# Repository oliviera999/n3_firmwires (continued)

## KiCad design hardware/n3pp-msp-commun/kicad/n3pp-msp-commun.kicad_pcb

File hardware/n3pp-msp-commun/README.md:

# Carte commune n3pp + msp (KiCad)

**Un seul PCB pour deux stations** : la serre/élevage (**n3pp**) et la station météo
(**msp**) partagent cette carte porteuse pour **ESP32 DevKit V1 30 broches**. Les deux
brochages firmware forment une **union disjointe vérifiée** (aucun GPIO utilisé pour deux
usages différents) : les firmwares actuels tournent **sans aucune modification**, c'est le
**profil d'assemblage** (quels composants on soude) qui spécialise la carte.

```
pinmap.json                  Source de vérité (union n3pp_config.h + msp_config.h, profils par broche)
kicad/n3pp-msp-commun.*      Projet KiCad 8 (schéma, PCB ROUTÉ) — ouvrable KiCad 8/9/10
BOM.csv                      Nomenclature (séparateur ;) avec colonne Profil
ACHATS.md                    Liste d'achat complète par profil (BOM + périphériques + boîtier + outillage)
ASSEMBLAGE-N3PP.md           Feuille d'assemblage générée : quoi souder pour une station n3pp
ASSEMBLAGE-MSP.md            Feuille d'assemblage générée : quoi souder pour une station msp
exports/gerbers-*.zip        Fabrication (Gerbers + perçages) — 210 x 105 mm, 2 couches, rev 0.2
exports/schema.pdf, pcb-*.svg   Rendus pour revue sans KiCad
fritzing/*.fzz               Vue breadboard du câblage (Fritzing >= 1.0)
generator/generate.py        Régénère schéma + PCB (non routé) + BOM + feuilles d'assemblage
generator/route_lv.py        Pipeline de routage (freerouting + couture GND + reliefs)
generator/tidy_silkscreen.py  Range la sérigraphie (repères vs étiquettes)
generator/export_fab.py      Export Gerbers/perçages prêts fabricant + rendus
generator/generate_fritzing.py  Régénère le .fzz de câblage
tools/check_pinmap_vs_firmware.py   Garde anti-dérive DOUBLE : n3pp_config.h ET msp_config.h ↔ plan
```

## Le principe : une base, deux profils

| Profil | Composants à souder | Le firmware tourne tel quel ? |
|---|---|---|
| **commun** | DevKit + alim + **interrupteur d'alim capteurs (GPIO13)** + 5 entrées ADC + pont batterie commuté + I2C/OLED + breakout + distribution | — (socle des deux profils) |
| **n3pp** | + REL2 (pompe GPIO12) + DHT GPIO18 | ✅ `pio run -e esp32dev` (n3pp) |
| **msp** | + servos tracker + 2 DHT + DS18B20 + pluie + 10k LDR | ✅ `pio run -e esp32dev` (msp) |
| **extension** | REL3..REL6 (GPIO 16/17/19/23), à activer côté firmware plus tard | provision matérielle |

Aucun strap, aucun interrupteur : les GPIO des deux firmwares ne se marchent jamais
dessus (voir la table ci-dessous), on peuple ou pas. Les feuilles
[`ASSEMBLAGE-N3PP.md`](ASSEMBLAGE-N3PP.md) / [`ASSEMBLAGE-MSP.md`](ASSEMBLAGE-MSP.md)
sont **générées depuis le même code que le PCB** : elles ne peuvent pas dériver du plan.

## Table des broches (union disjointe)

| GPIO | Bloc carte | n3pp (`n3pp_config.h`) | msp (`msp_config.h`) |
|---|---|---|---|
| 13 | **Interrupteur d'alim capteurs** (Q1+Q7 P-MOSFET → rail `+3V3_SW`) | `RELAIS` | `RELAIS` |
| 12 | **REL2** (strapping MTDI → pull-down base 10k) | `POMPE` | — |
| 16/17/19/23 | **REL3..REL6** extensions AUX | — | — |
| 18 | DHT n3pp (JST, pull-up 10k) | `DHTPIN` | — |
| 26 / 15 | DHT INT / EXT (JST, pull-ups 10k) | — | `DHTPININT` / `DHTPINEXT` |
| 2 | 1-Wire DS18B20 (bornier, pull-up 4,7k) ⚠️ strapping | — | `oneWireBus` |
| 27 | Pluie — **sortie DO numérique** (ADC2 ≠ WiFi) | — | `PLUIE` |
| 33/32/35/34/39 | **ADC A..E** (borniers 3V3/AIN/GND) | `humidite1..4`, `LUMINOSITE` | `LUMINOSITEa..d`, `HumiditeSol` |
| 36 (VP) | Pont batterie 2,2k/2,2k (bornier VBAT/GND) | `pontdiv` | `pontdiv` |
| 25 / 14 | Servos tracker (headers, série 220R) | — | `SERVOGD` / `SERVOHB` |
| 21 / 22 | I2C : OLED 0x3C + **3 ports libres** (pull-ups 4,7k) | ✅ | ✅ |
| 4, 5, EN, RX0, TX0 | **Breakout J18** (tous les GPIO restants) | libres | libres |

## Les demandes spécifiques de cette carte

- **Rail capteurs commuté (rev 0.2)** : les deux firmwares utilisent GPIO13 comme
  *power-gate* (mis à 1 au réveil, relâché en deep sleep — vérifié dans les sources).
  La carte le câble sur un **interrupteur haut P-MOSFET** (Q1 BC337 + Q7 NDP6020P) qui
  coupe `+3V3_SW` — capteurs, OLED, ports I2C **et leurs pull-ups** — pendant la veille.
  Le **pont diviseur batterie est commuté lui aussi** (Q8 BS250 côté haut + Q9), donc
  ~0 µA de fuite en veille, et jamais plus de 3,3 V sur GPIO36 pont coupé.
- **5 canaux relais** embarqués (BC337 + 1N4007 + LED témoin + bornier NO/COM/NC) :
  REL2 piloté par n3pp (pompe), REL3..REL6 en réserve sur des GPIO **non-strapping** —
  à activer côté firmware comme AUX1/AUX2 de ffp5cs, sans retoucher la carte.
- **Connexions I2C supplémentaires** : OLED + 3 ports libres (J15/J16/J17, brochage
  GND/VCC/SCL/SDA), 3-4 modules simultanés avec les pull-ups 4,7 k.
- **Toutes les broches restantes utilisables** : breakout J18 (`3V3 GND EN IO4 IO5 RX0
  TX0` — RX0/TX0 à laisser libres pendant un flash USB), rail d'alim Dupont J19
  (2×5V 2×GND 2×3V3), borniers de distribution 5 V (J28) et 3V3 (J29).
- **Zéro soudure à l'usage** : DevKit socketé, charges sur borniers à vis, capteurs sur
  JST-XH/borniers, servos/OLED/GPIO en headers.

## Pièges connus (hérités des firmwares, choix assumés)

- **GPIO2 (1-Wire msp)** est une broche de strapping : le pull-up 4,7 k peut gêner le
  passage en mode flash. Si le flash USB échoue, débrancher la sonde DS18B20 le temps du
  flash. (Conservé pour rester compatible avec le firmware msp actuel.)
- **GPIO27 (pluie msp)** est sur ADC2, inutilisable en analogique quand le WiFi est actif :
  brancher la sortie **DO** (numérique) du module pluie, pas AO — lue en `digitalRead`
  par le firmware msp ≥ 2.72 (projection 4095 sec / 100 mouillé, contrat serveur inchangé).
- **GPIO12 (pompe n3pp)** est strapping MTDI : le pull-down de base du canal REL2 garantit
  l'état sûr au boot.
- **JP1 (cavalier 3V3)** : en alimentation batterie/LDO par J29, RETIRER le cavalier
  avant de brancher l'USB du DevKit (sinon deux régulateurs se disputent le rail).
- Profils **sur batterie (18650 + TP4056 solaire)** : ne pas peupler les LED témoin,
  et **ne jamais brancher la batterie brute sur J1/jack** (brownouts + relais 5 V) —
  boost 5 V → J1 si relais/servos, ou LDO 3,3 V → J29 sinon ; mesure VBAT → J27.
  Câblages, achats et autonomies chiffrées : [`ACHATS.md` §5 bis](ACHATS.md).

## Régénérer / rerouter / vérifier

```bash
cd hardware/n3pp-msp-commun
python3 generator/generate.py          # schéma + PCB placé (NON routé) + BOM + feuilles
python3 generator/route_lv.py          # autoroute, coud les masses, corrige les reliefs
python3 generator/tidy_silkscreen.py   # écarte les repères qui masquent une étiquette
python3 generator/export_fab.py        # zip Gerbers prêt JLCPCB + rendus de revue
python3 tools/check_pinmap_vs_firmware.py   # garde anti-dérive (les DEUX firmwares)
kicad-cli pcb drc --severity-error kicad/n3pp-msp-commun.kicad_pcb -o /tmp/drc.rpt
```

⚠️ `generate.py` écrase le PCB routé — enchaîner systématiquement avec `route_lv.py`.
Le routage livré dans `kicad/` est déjà fait et validé (DRC 0 violation).

Empreintes : bibliothèque officielle KiCad 8.0.9 (CC-BY-SA 4.0 + exception d'usage),
vendorées dans `generator/footprints/`.

Commander les cartes : voir **[../COMMANDE_JLCPCB.md](../COMMANDE_JLCPCB.md)**
(réglages du formulaire, options utiles, pourquoi 1 oz ici et 2 oz sur la 230 V).

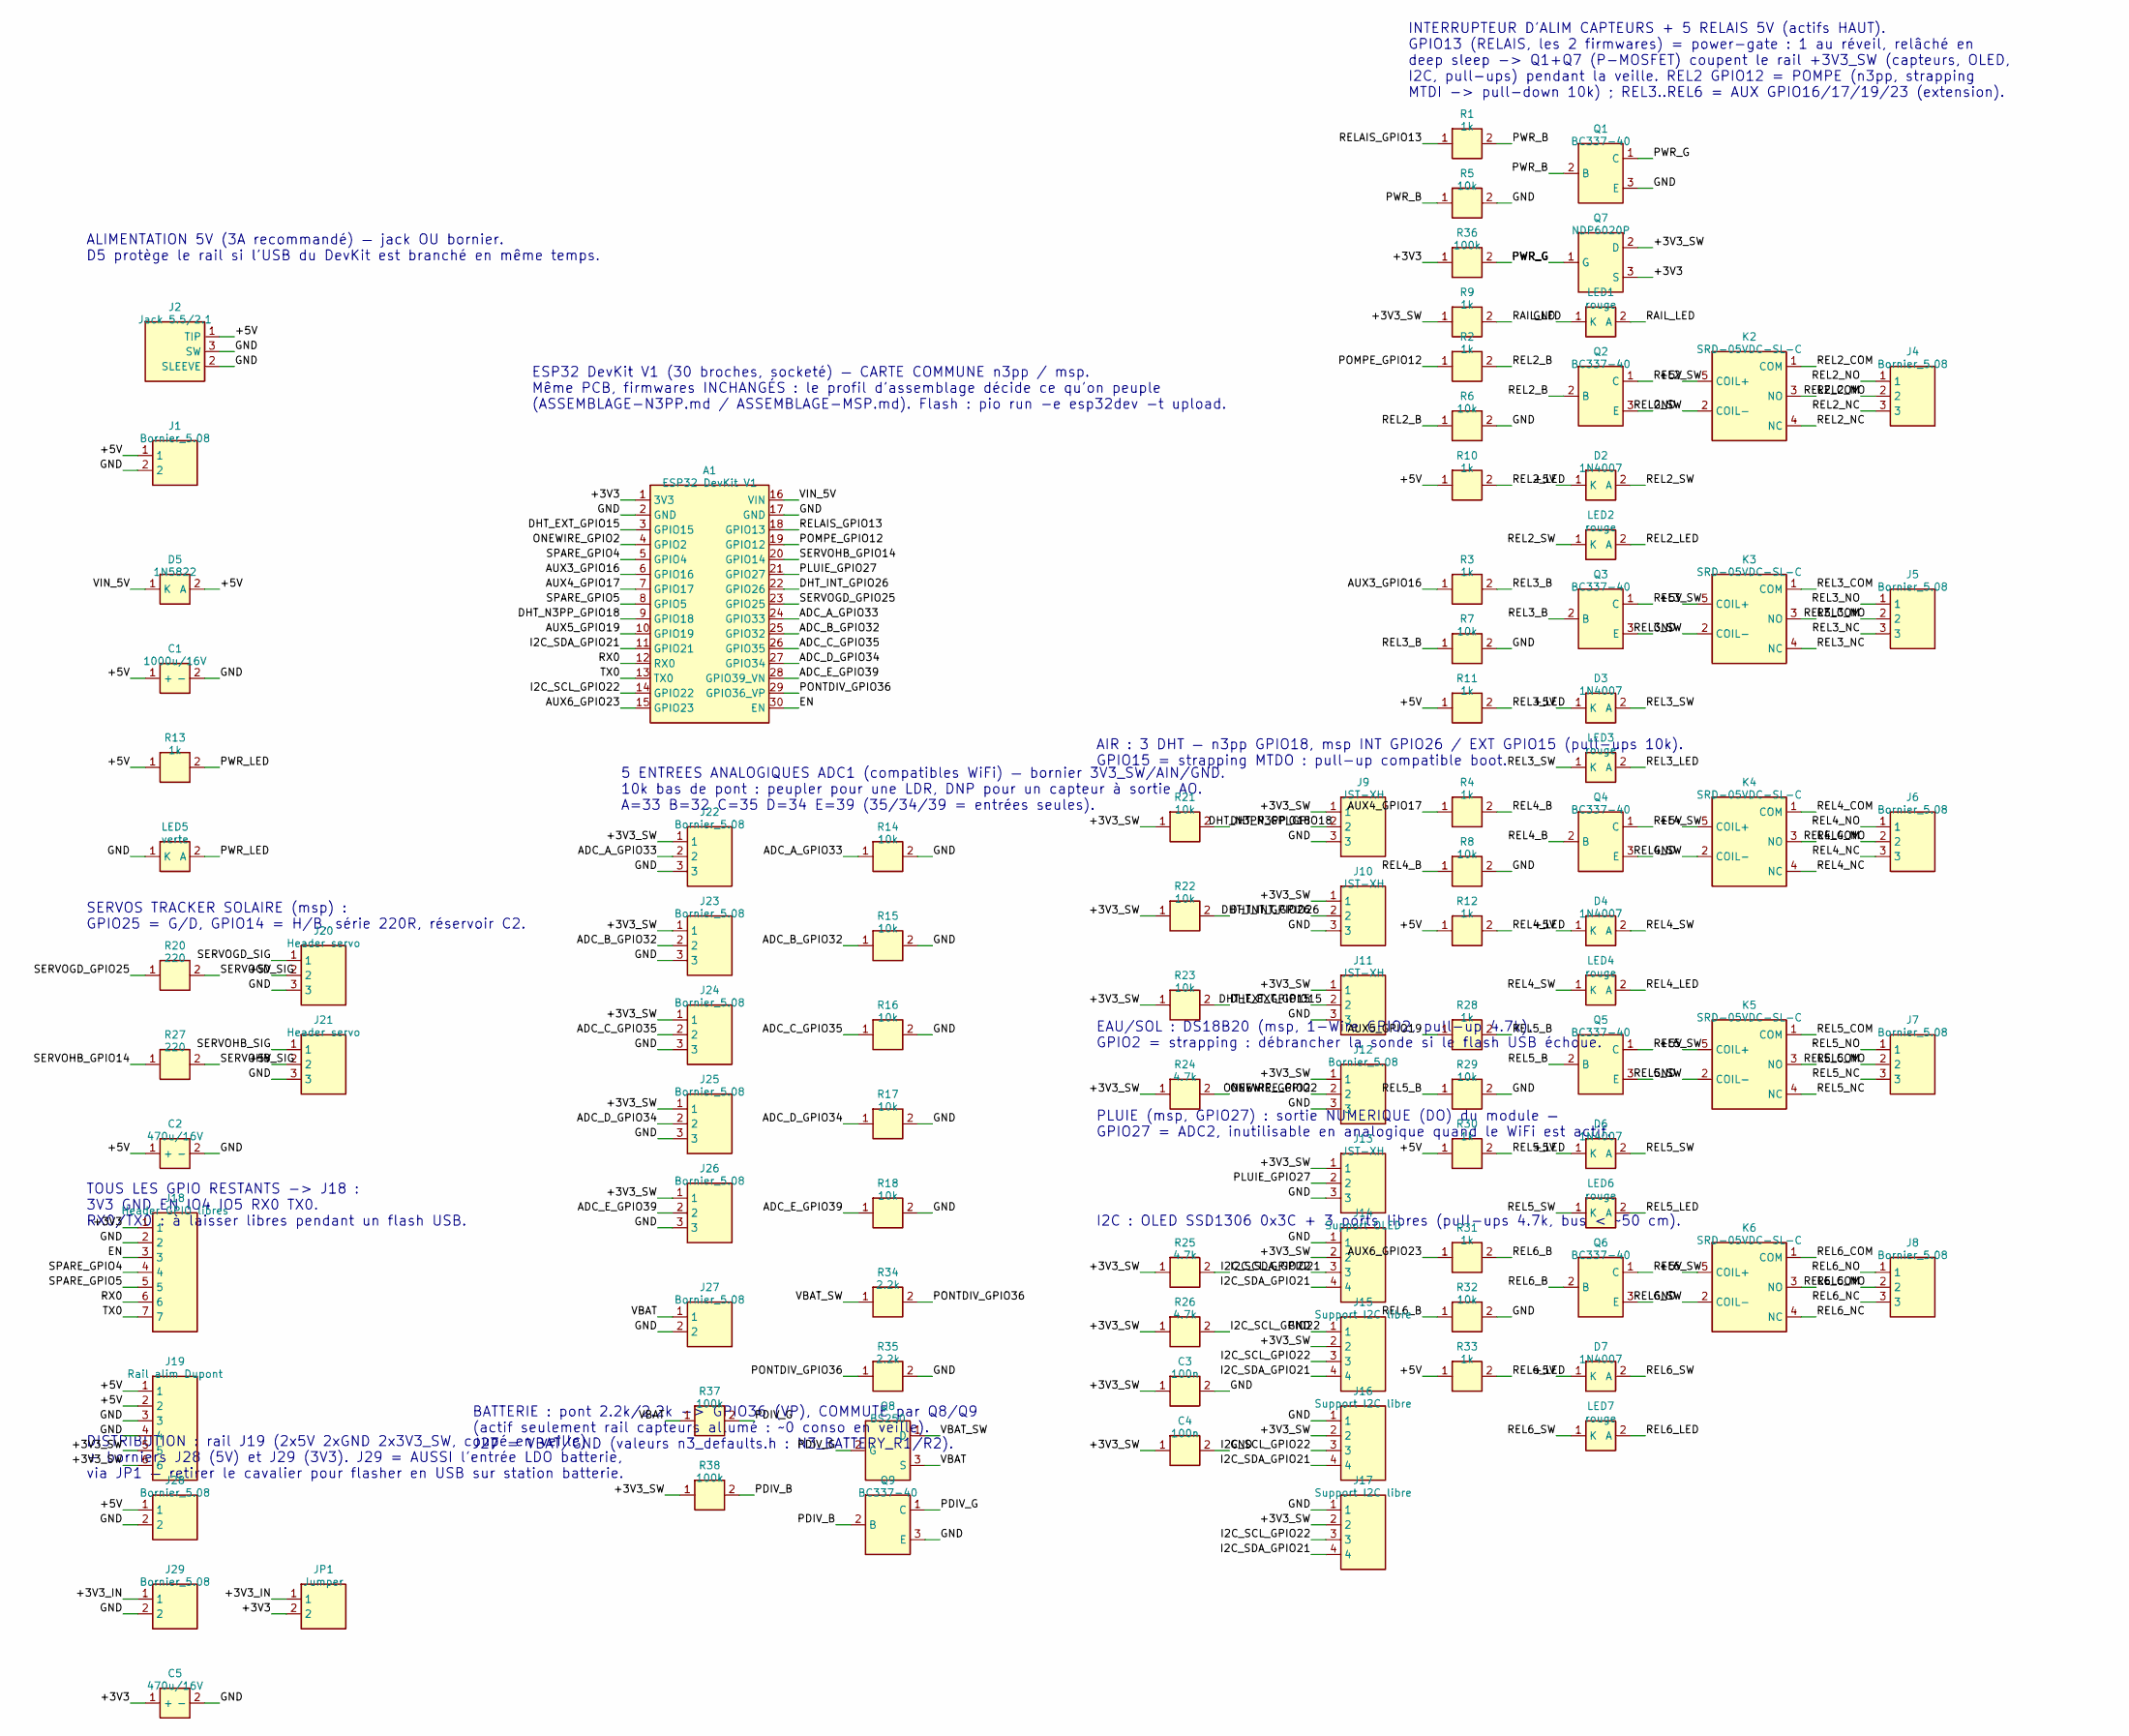
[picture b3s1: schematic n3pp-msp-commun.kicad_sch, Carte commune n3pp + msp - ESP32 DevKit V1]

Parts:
A1: ESP32 DevKit V1; ESP32_DevKit_V1_30pin
C1: 1000u/16V; CP_Radial_D10.0mm_P5.00mm
C2, C5: 470u/16V; CP_Radial_D8.0mm_P3.50mm
C3, C4: 100n; C_Disc_D5.0mm_W2.5mm_P5.00mm
D2, D3, D4, D6, D7: 1N4007; D_DO-41_SOD81_P10.16mm_Horizontal
D5: 1N5822; D_DO-201AD_P15.24mm_Horizontal
J1, J27, J28, J29: Bornier_5.08; TerminalBlock_bornier-2_P5.08mm
J2: Jack 5.5/2.1; BarrelJack_Horizontal
J4, J5, J6, J7, J8, J12, J22, J23, J24, J25, J26: Bornier_5.08; TerminalBlock_bornier-3_P5.08mm
J9, J10, J11, J13: JST-XH; JST_XH_B3B-XH-A_1x03_P2.50mm_Vertical
J14: Support OLED; PinSocket_1x04_P2.54mm_Vertical
J15, J16, J17: Support I2C libre; PinSocket_1x04_P2.54mm_Vertical
J18: Header GPIO libres; PinHeader_1x07_P2.54mm_Vertical
J19: Rail alim Dupont; PinHeader_1x06_P2.54mm_Vertical
J20, J21: Header servo; PinHeader_1x03_P2.54mm_Vertical
JP1: Jumper; PinHeader_1x02_P2.54mm_Vertical
K2, K3, K4, K5, K6: SRD-05VDC-SL-C; Relay_SPDT_SANYOU_SRD_Series_Form_C
LED1, LED2, LED3, LED4, LED6, LED7: rouge; LED_D5.0mm
LED5: verte; LED_D5.0mm
Q1, Q2, Q3, Q4, Q5, Q6, Q9: BC337-40; TO-92_Inline
Q7: NDP6020P; TO-220-3_Vertical
Q8: BS250; TO-92_Inline
R1, R2, R3, R4, R9, R10, R11, R12, R13, R28, R30, R31, R33: 1k; R_Axial_DIN0207_L6.3mm_D2.5mm_P10.16mm_Horizontal
R5, R6, R7, R8, R14, R15, R16, R17, R18, R21, R22, R23, R29, R32: 10k; R_Axial_DIN0207_L6.3mm_D2.5mm_P10.16mm_Horizontal
R20, R27: 220; R_Axial_DIN0207_L6.3mm_D2.5mm_P10.16mm_Horizontal
R24, R25, R26: 4.7k; R_Axial_DIN0207_L6.3mm_D2.5mm_P10.16mm_Horizontal
R34, R35: 2.2k; R_Axial_DIN0207_L6.3mm_D2.5mm_P10.16mm_Horizontal
R36, R37, R38: 100k; R_Axial_DIN0207_L6.3mm_D2.5mm_P10.16mm_Horizontal

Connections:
+3V3: A1.1 (3V3), C5.1 (+), J18.1, JP1.2, Q7.3 (S), R36.1
+3V3_IN: J29.1, JP1.1
+3V3_SW: C3.1, C4.1, J9.1, J10.1, J11.1, J12.1, J13.1, J14.2, J15.2, J16.2, J17.2, J19.5, J19.6, J22.1, J23.1, J24.1, J25.1, J26.1, Q7.2 (D), R9.1, R21.1, R22.1, R23.1, R24.1, R25.1, R26.1, R38.1
+5V: C1.1 (+), C2.1 (+), D2.1 (K), D3.1 (K), D4.1 (K), D5.2 (A), D6.1 (K), D7.1 (K), J1.1, J2.1 (TIP), J19.1, J19.2, J20.2, J21.2, J28.1, K2.5 (COIL+), K3.5 (COIL+), K4.5 (COIL+), K5.5 (COIL+), K6.5 (COIL+), R10.1, R11.1, R12.1, R13.1, R30.1, R33.1
ADC_A_GPIO33: A1.24 (GPIO33), J22.2, R14.1
ADC_B_GPIO32: A1.25 (GPIO32), J23.2, R15.1
ADC_C_GPIO35: A1.26 (GPIO35), J24.2, R16.1
ADC_D_GPIO34: A1.27 (GPIO34), J25.2, R17.1
ADC_E_GPIO39: A1.28 (GPIO39_VN), J26.2, R18.1
AUX3_GPIO16: A1.6 (GPIO16), R3.1
AUX4_GPIO17: A1.7 (GPIO17), R4.1
AUX5_GPIO19: A1.10 (GPIO19), R28.1
AUX6_GPIO23: A1.15 (GPIO23), R31.1
DHT_EXT_GPIO15: A1.3 (GPIO15), J11.2, R23.2
DHT_INT_GPIO26: A1.22 (GPIO26), J10.2, R22.2
DHT_N3PP_GPIO18: A1.9 (GPIO18), J9.2, R21.2
EN: A1.30 (EN), J18.3
GND: A1.2 (GND), A1.17 (GND), C1.2 (-), C2.2 (-), C3.2, C4.2, C5.2 (-), J1.2, J2.2 (SLEEVE), J2.3 (SW), J9.3, J10.3, J11.3, J12.3, J13.3, J14.1, J15.1, J16.1, J17.1, J18.2, J19.3, J19.4, J20.3, J21.3, J22.3, J23.3, J24.3, J25.3, J26.3, J27.2, J28.2, J29.2, LED1.1 (K), LED5.1 (K), Q1.3 (E), Q2.3 (E), Q3.3 (E), Q4.3 (E), Q5.3 (E), Q6.3 (E), Q9.3 (E), R5.2, R6.2, R7.2, R8.2, R14.2, R15.2, R16.2, R17.2, R18.2, R29.2, R32.2, R35.2
I2C_SCL_GPIO22: A1.14 (GPIO22), J14.3, J15.3, J16.3, J17.3, R26.2
I2C_SDA_GPIO21: A1.11 (GPIO21), J14.4, J15.4, J16.4, J17.4, R25.2
ONEWIRE_GPIO2: A1.4 (GPIO2), J12.2, R24.2
PDIV_B: Q9.2 (B), R38.2
PDIV_G: Q8.2 (G), Q9.1 (C), R37.2
PLUIE_GPIO27: A1.21 (GPIO27), J13.2
POMPE_GPIO12: A1.19 (GPIO12), R2.1
PONTDIV_GPIO36: A1.29 (GPIO36_VP), R34.2, R35.1
PWR_B: Q1.2 (B), R1.2, R5.1
PWR_G: Q1.1 (C), Q7.1 (G), R36.2
PWR_LED: LED5.2 (A), R13.2
RAIL_LED: LED1.2 (A), R9.2
REL2_B: Q2.2 (B), R2.2, R6.1
REL2_COM: J4.2, K2.1 (COM)
REL2_LED: LED2.2 (A), R10.2
REL2_NC: J4.3, K2.4 (NC)
REL2_NO: J4.1, K2.3 (NO)
REL2_SW: D2.2 (A), K2.2 (COIL-), LED2.1 (K), Q2.1 (C)
REL3_B: Q3.2 (B), R3.2, R7.1
REL3_COM: J5.2, K3.1 (COM)
REL3_LED: LED3.2 (A), R11.2
REL3_NC: J5.3, K3.4 (NC)
REL3_NO: J5.1, K3.3 (NO)
REL3_SW: D3.2 (A), K3.2 (COIL-), LED3.1 (K), Q3.1 (C)
REL4_B: Q4.2 (B), R4.2, R8.1
REL4_COM: J6.2, K4.1 (COM)
REL4_LED: LED4.2 (A), R12.2
REL4_NC: J6.3, K4.4 (NC)
REL4_NO: J6.1, K4.3 (NO)
REL4_SW: D4.2 (A), K4.2 (COIL-), LED4.1 (K), Q4.1 (C)
REL5_B: Q5.2 (B), R28.2, R29.1
REL5_COM: J7.2, K5.1 (COM)
REL5_LED: LED6.2 (A), R30.2
REL5_NC: J7.3, K5.4 (NC)
REL5_NO: J7.1, K5.3 (NO)
REL5_SW: D6.2 (A), K5.2 (COIL-), LED6.1 (K), Q5.1 (C)
REL6_B: Q6.2 (B), R31.2, R32.1
REL6_COM: J8.2, K6.1 (COM)
REL6_LED: LED7.2 (A), R33.2
REL6_NC: J8.3, K6.4 (NC)
REL6_NO: J8.1, K6.3 (NO)
REL6_SW: D7.2 (A), K6.2 (COIL-), LED7.1 (K), Q6.1 (C)
RELAIS_GPIO13: A1.18 (GPIO13), R1.1
RX0: A1.12 (RX0), J18.6
SERVOGD_GPIO25: A1.23 (GPIO25), R20.1
SERVOGD_SIG: J20.1, R20.2
SERVOHB_GPIO14: A1.20 (GPIO14), R27.1
SERVOHB_SIG: J21.1, R27.2
SPARE_GPIO4: A1.5 (GPIO4), J18.4
SPARE_GPIO5: A1.8 (GPIO5), J18.5
TX0: A1.13 (TX0), J18.7
VBAT: J27.1, Q8.3 (S), R37.1
VBAT_SW: Q8.1 (D), R34.1
VIN_5V: A1.16 (VIN), D5.1 (K)

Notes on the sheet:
ALIMENTATION 5V (3A recommandé) — jack OU bornier. D5 protège le rail si l'USB du DevKit est branché en même temps.
ESP32 DevKit V1 (30 broches, socketé) — CARTE COMMUNE n3pp / msp. Même PCB, firmwares INCHANGÉS : le profil d'assemblage décide ce qu'on peuple (ASSEMBLAGE-N3PP.md / ASSEMBLAGE-MSP.md). Flash : pio run -e esp32dev -t upload.
5 ENTREES ANALOGIQUES ADC1 (compatibles WiFi) — bornier 3V3_SW/AIN/GND. 10k bas de pont : peupler pour une LDR, DNP pour un capteur à sortie AO. A=33 B=32 C=35 D=34 E=39 (35/34/39 = entrées seules).
BATTERIE : pont 2.2k/2.2k -> GPIO36 (VP), COMMUTE par Q8/Q9 (actif seulement rail capteurs allumé : ~0 conso en veille). J27 = VBAT/GND (valeurs n3_defaults.h : N3_BATTERY_R1/R2).
SERVOS TRACKER SOLAIRE (msp) : GPIO25 = G/D, GPIO14 = H/B, série 220R, réservoir C2.
TOUS LES GPIO RESTANTS -> J18 : 3V3 GND EN IO4 IO5 RX0 TX0. RX0/TX0 : à laisser libres pendant un flash USB.
DISTRIBUTION : rail J19 (2x5V 2xGND 2x3V3_SW, coupé en veille) + borniers J28 (5V) et J29 (3V3). J29 = AUSSI l'entrée LDO batterie, via JP1 — retirer le cavalier pour flasher en USB sur station batterie.
AIR : 3 DHT — n3pp GPIO18, msp INT GPIO26 / EXT GPIO15 (pull-ups 10k). GPIO15 = strapping MTDO : pull-up compatible boot.
EAU/SOL : DS18B20 (msp, 1-Wire GPIO2, pull-up 4.7k). GPIO2 = strapping : débrancher la sonde si le flash USB échoue.
PLUIE (msp, GPIO27) : sortie NUMERIQUE (DO) du module — GPIO27 = ADC2, inutilisable en analogique quand le WiFi est actif.
I2C : OLED SSD1306 0x3C + 3 ports libres (pull-ups 4.7k, bus < ~50 cm).
INTERRUPTEUR D'ALIM CAPTEURS + 5 RELAIS 5V (actifs HAUT). GPIO13 (RELAIS, les 2 firmwares) = power-gate : 1 au réveil, relâché en deep sleep -> Q1+Q7 (P-MOSFET) coupent le rail +3V3_SW (capteurs, OLED, I2C, pull-ups) pendant la veille. REL2 GPIO12 = POMPE (n3pp, strapping MTDI -> pull-down 10k) ; R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

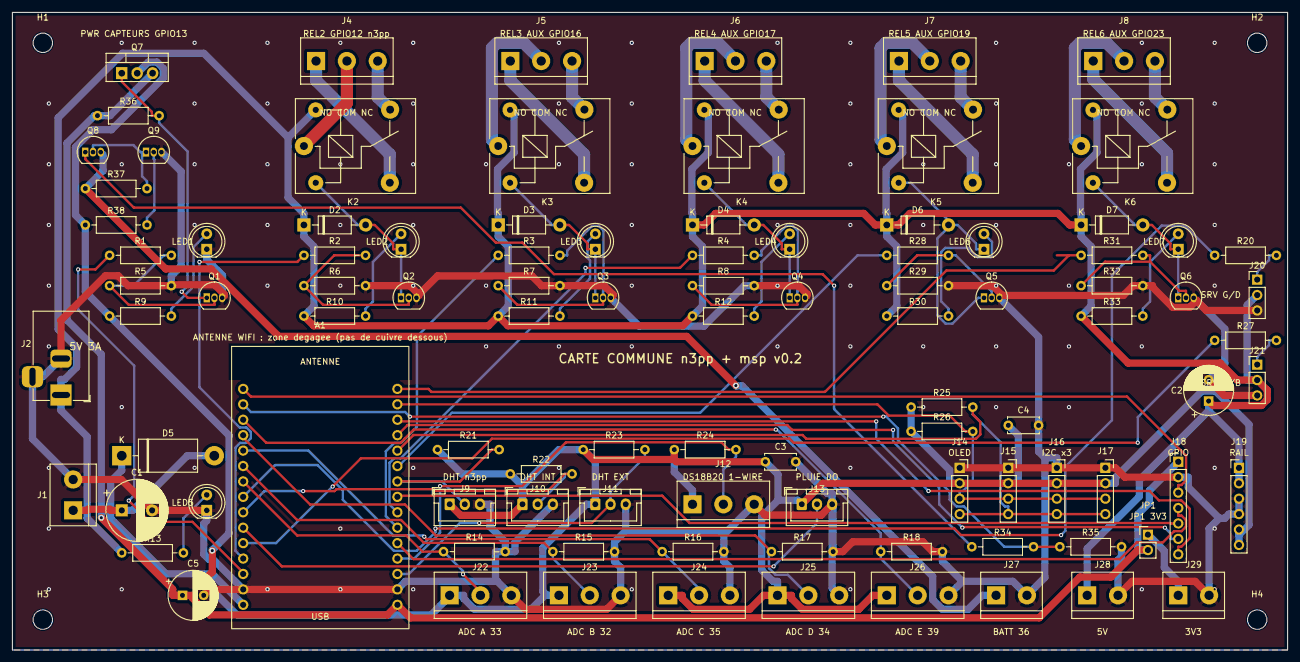
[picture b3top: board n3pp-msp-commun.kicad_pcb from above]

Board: 2 copper layers, 210.0 x 105.0 mm, 103 parts (0 on the bottom side), 72 nets.

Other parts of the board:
H1, H2, H3, H4: M3; MountingHole_3.2mm_M3

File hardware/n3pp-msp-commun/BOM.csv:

Refs;Qte;Valeur;Empreinte;Description;Profil
A1;1;ESP32 DevKit V1;ESP32_DevKit_V1_30pin;Module ESP32-WROOM-32 DevKit V1 30 broches, sur 2 supports 1x15;commun (toujours)
C1;1;1000u/16V;CP_Radial_D10.0mm_P5.00mm;Réservoir rail 5V (relais + servos + WiFi);commun (toujours)
C2;1;470u/16V;CP_Radial_D8.0mm_P3.50mm;Découplage rail 5V servos;profil msp
C3;1;100n;C_Disc_D5.0mm_W2.5mm_P5.00mm;Découplage 3V3 capteurs;commun (toujours)
C4;1;100n;C_Disc_D5.0mm_W2.5mm_P5.00mm;Découplage 3V3 I2C;commun (toujours)
D1;1;1N4007;D_DO-41_SOD81_P10.16mm_Horizontal;Diode de roue libre bobine;commun (toujours)
D2;1;1N4007;D_DO-41_SOD81_P10.16mm_Horizontal;Diode de roue libre bobine;profil n3pp
D3 D4 D6 D7;4;1N4007;D_DO-41_SOD81_P10.16mm_Horizontal;Diode de roue libre bobine;extension (option)
D5;1;1N5822;D_DO-201AD_P15.24mm_Horizontal;Schottky 3A vers VIN DevKit (anti-retour si USB branché);commun (toujours)
H1 H2 H3 H4;4;M3;MountingHole_3.2mm_M3;Trou de fixation M3;commun (toujours)
J1;1;Bornier_5.08;TerminalBlock_bornier-2_P5.08mm;Entrée 5V alternative (bornier, 1=+5V 2=GND);commun (toujours)
J10;1;JST-XH;JST_XH_B3B-XH-A_1x03_P2.50mm_Vertical;DHT INT msp (1=3V3 2=DATA 3=GND);profil msp
J11;1;JST-XH;JST_XH_B3B-XH-A_1x03_P2.50mm_Vertical;DHT EXT msp (1=3V3 2=DATA 3=GND);profil msp
J12;1;Bornier_5.08;TerminalBlock_bornier-3_P5.08mm;Sonde DS18B20 étanche (1=3V3 2=DATA 3=GND);profil msp
J13;1;JST-XH;JST_XH_B3B-XH-A_1x03_P2.50mm_Vertical;Capteur pluie — sortie NUMERIQUE DO (1=3V3 2=DO 3=GND);profil msp
J14;1;Support OLED;PinSocket_1x04_P2.54mm_Vertical;OLED SSD1306 128x64 I2C 0x3C (1=GND 2=VCC 3=SCL 4=SDA);commun (toujours)
J15;1;Support I2C libre;PinSocket_1x04_P2.54mm_Vertical;Port I2C libre 1 (1=GND 2=VCC 3=SCL 4=SDA);commun (toujours)
J16;1;Support I2C libre;PinSocket_1x04_P2.54mm_Vertical;Port I2C libre 2 (1=GND 2=VCC 3=SCL 4=SDA);commun (toujours)
J17;1;Support I2C libre;PinSocket_1x04_P2.54mm_Vertical;Port I2C libre 3 (1=GND 2=VCC 3=SCL 4=SDA);commun (toujours)
J18;1;Header GPIO libres;PinHeader_1x07_P2.54mm_Vertical;GPIO libres (1=3V3 2=GND 3=EN 4=IO4 5=IO5 6=RX0 7=TX0);commun (toujours)
J19;1;Rail alim Dupont;PinHeader_1x06_P2.54mm_Vertical;Rail alim modules (1=5V 2=5V 3=GND 4=GND 5=3V3 6=3V3);commun (toujours)
J2;1;Jack 5.5/2.1;BarrelJack_Horizontal;Entrée 5V 3A (jack, centre = +);commun (toujours)
J20;1;Header servo;PinHeader_1x03_P2.54mm_Vertical;Servo G/D tracker (1=SIG 2=+5V 3=GND);profil msp
J21;1;Header servo;PinHeader_1x03_P2.54mm_Vertical;Servo H/B tracker (1=SIG 2=+5V 3=GND);profil msp
J22;1;Bornier_5.08;TerminalBlock_bornier-3_P5.08mm;Entrée ADC_A (1=3V3 2=AIN 3=GND) — n3pp: humidite1 (sol) / msp: LUMINOSITEa (LDR);commun (toujours)
J23;1;Bornier_5.08;TerminalBlock_bornier-3_P5.08mm;Entrée ADC_B (1=3V3 2=AIN 3=GND) — n3pp: humidite2 (sol) / msp: HumiditeSol (module AO);commun (toujours)
J24;1;Bornier_5.08;TerminalBlock_bornier-3_P5.08mm;Entrée ADC_C (1=3V3 2=AIN 3=GND) — n3pp: humidite3 (sol) / msp: LUMINOSITEc (LDR);commun (toujours)
J25;1;Bornier_5.08;TerminalBlock_bornier-3_P5.08mm;Entrée ADC_D (1=3V3 2=AIN 3=GND) — n3pp: humidite4 (sol) / msp: LUMINOSITEb (LDR);commun (toujours)
J26;1;Bornier_5.08;TerminalBlock_bornier-3_P5.08mm;Entrée ADC_E (1=3V3 2=AIN 3=GND) — n3pp: LUMINOSITE (LDR) / msp: LUMINOSITEd (LDR);commun (toujours)
J27;1;Bornier_5.08;TerminalBlock_bornier-2_P5.08mm;Mesure batterie (1=VBAT 2=GND, pont 2.2k/2.2k -> GPIO36);commun (toujours)
J28;1;Bornier_5.08;TerminalBlock_bornier-2_P5.08mm;Distribution 5V (1=+5V 2=GND);commun (toujours)
J29;1;Bornier_5.08;TerminalBlock_bornier-2_P5.08mm;Distribution 3V3 (1=+3V3 2=GND);commun (toujours)
J3;1;Bornier_5.08;TerminalBlock_bornier-3_P5.08mm;Bornier charge (1=NO 2=COM 3=NC);commun (toujours)
J4;1;Bornier_5.08;TerminalBlock_bornier-3_P5.08mm;Bornier charge (1=NO 2=COM 3=NC);profil n3pp
J5 J6 J7 J8;4;Bornier_5.08;TerminalBlock_bornier-3_P5.08mm;Bornier charge (1=NO 2=COM 3=NC);extension (option)
J9;1;JST-XH;JST_XH_B3B-XH-A_1x03_P2.50mm_Vertical;DHT n3pp (1=3V3 2=DATA 3=GND);profil n3pp
K1;1;SRD-05VDC-SL-C;Relay_SPDT_SANYOU_SRD_Series_Form_C;Relais 5V SPDT 10A (Songle/Sanyou SRD);commun (toujours)
K2;1;SRD-05VDC-SL-C;Relay_SPDT_SANYOU_SRD_Series_Form_C;Relais 5V SPDT 10A (Songle/Sanyou SRD);profil n3pp
K3 K4 K5 K6;4;SRD-05VDC-SL-C;Relay_SPDT_SANYOU_SRD_Series_Form_C;Relais 5V SPDT 10A (Songle/Sanyou SRD);extension (option)
LED1;1;rouge;LED_D5.0mm;LED témoin relais ON (DNP si profil batterie);commun (toujours)
LED2;1;rouge;LED_D5.0mm;LED témoin relais ON (DNP si profil batterie);profil n3pp
LED3 LED4 LED6 LED7;4;rouge;LED_D5.0mm;LED témoin relais ON (DNP si profil batterie);extension (option)
LED5;1;verte;LED_D5.0mm;LED présence 5V (DNP si profil batterie);commun (toujours)
Q1;1;BC337-40;TO-92_Inline;Transistor NPN commande relais (1=C 2=B 3=E);commun (toujours)
Q2;1;BC337-40;TO-92_Inline;Transistor NPN commande relais (1=C 2=B 3=E);profil n3pp
Q3 Q4 Q5 Q6;4;BC337-40;TO-92_Inline;Transistor NPN commande relais (1=C 2=B 3=E);extension (option)
R1;1;1k;R_Axial_DIN0207_L6.3mm_D2.5mm_P10.16mm_Horizontal;Résistance base transistor;commun (toujours)
R10;1;1k;R_Axial_DIN0207_L6.3mm_D2.5mm_P10.16mm_Horizontal;Résistance LED témoin (DNP si profil batterie);profil n3pp
R11 R12 R30 R33;4;1k;R_Axial_DIN0207_L6.3mm_D2.5mm_P10.16mm_Horizontal;Résistance LED témoin (DNP si profil batterie);extension (option)
R13;1;1k;R_Axial_DIN0207_L6.3mm_D2.5mm_P10.16mm_Horizontal;Résistance LED présence 5V (DNP si profil batterie);commun (toujours)
R14;1;10k;R_Axial_DIN0207_L6.3mm_D2.5mm_P10.16mm_Horizontal;"Bas de pont ADC_A (peupler si LDR ; DNP si capteur AO)";profil msp
R15;1;10k;R_Axial_DIN0207_L6.3mm_D2.5mm_P10.16mm_Horizontal;"Bas de pont ADC_B (peupler si LDR ; DNP si capteur AO)";extension (option)
R16;1;10k;R_Axial_DIN0207_L6.3mm_D2.5mm_P10.16mm_Horizontal;"Bas de pont ADC_C (peupler si LDR ; DNP si capteur AO)";profil msp
R17;1;10k;R_Axial_DIN0207_L6.3mm_D2.5mm_P10.16mm_Horizontal;"Bas de pont ADC_D (peupler si LDR ; DNP si capteur AO)";profil msp
R18;1;10k;R_Axial_DIN0207_L6.3mm_D2.5mm_P10.16mm_Horizontal;"Bas de pont ADC_E (peupler si LDR ; DNP si capteur AO)";commun (toujours)
R2;1;1k;R_Axial_DIN0207_L6.3mm_D2.5mm_P10.16mm_Horizontal;Résistance base transistor;profil n3pp
R20;1;220;R_Axial_DIN0207_L6.3mm_D2.5mm_P10.16mm_Horizontal;Série signal servo G/D (GPIO25);profil msp
R21;1;10k;R_Axial_DIN0207_L6.3mm_D2.5mm_P10.16mm_Horizontal;Pull-up data DHT n3pp;profil n3pp
R22;1;10k;R_Axial_DIN0207_L6.3mm_D2.5mm_P10.16mm_Horizontal;Pull-up data DHT INT msp;profil msp
R23;1;10k;R_Axial_DIN0207_L6.3mm_D2.5mm_P10.16mm_Horizontal;Pull-up data DHT EXT msp;profil msp
R24;1;4.7k;R_Axial_DIN0207_L6.3mm_D2.5mm_P10.16mm_Horizontal;Pull-up bus 1-Wire DS18B20;profil msp
R25;1;4.7k;R_Axial_DIN0207_L6.3mm_D2.5mm_P10.16mm_Horizontal;Pull-up I2C SDA;commun (toujours)
R26;1;4.7k;R_Axial_DIN0207_L6.3mm_D2.5mm_P10.16mm_Horizontal;Pull-up I2C SCL;commun (toujours)
R27;1;220;R_Axial_DIN0207_L6.3mm_D2.5mm_P10.16mm_Horizontal;Série signal servo H/B (GPIO14);profil msp
R28 R3 R31 R4;4;1k;R_Axial_DIN0207_L6.3mm_D2.5mm_P10.16mm_Horizontal;Résistance base transistor;extension (option)
R34;1;2.2k;R_Axial_DIN0207_L6.3mm_D2.5mm_P10.16mm_Horizontal;Pont batterie haut (N3_BATTERY_R1=2200);commun (toujours)
R35;1;2.2k;R_Axial_DIN0207_L6.3mm_D2.5mm_P10.16mm_Horizontal;Pont batterie bas (N3_BATTERY_R2=2180, 2.2k mesurée);commun (toujours)
R5;1;10k;R_Axial_DIN0207_L6.3mm_D2.5mm_P10.16mm_Horizontal;Pull-down base (état sûr au boot);commun (toujours)
R6;1;10k;R_Axial_DIN0207_L6.3mm_D2.5mm_P10.16mm_Horizontal;Pull-down base (état sûr au boot);profil n3pp
R29 R32 R7 R8;4;10k;R_Axial_DIN0207_L6.3mm_D2.5mm_P10.16mm_Horizontal;Pull-down base (état sûr au boot);extension (option)
R9;1;1k;R_Axial_DIN0207_L6.3mm_D2.5mm_P10.16mm_Horizontal;Résistance LED témoin (DNP si profil batterie);commun (toujours)
A1 (supports);2;Support femelle 1x15 P2.54;monte sur l'empreinte ESP32_DevKit_V1_30pin;Barrettes femelles 15 pts : le DevKit s'enfiche, jamais soudé;commun (toujours)
